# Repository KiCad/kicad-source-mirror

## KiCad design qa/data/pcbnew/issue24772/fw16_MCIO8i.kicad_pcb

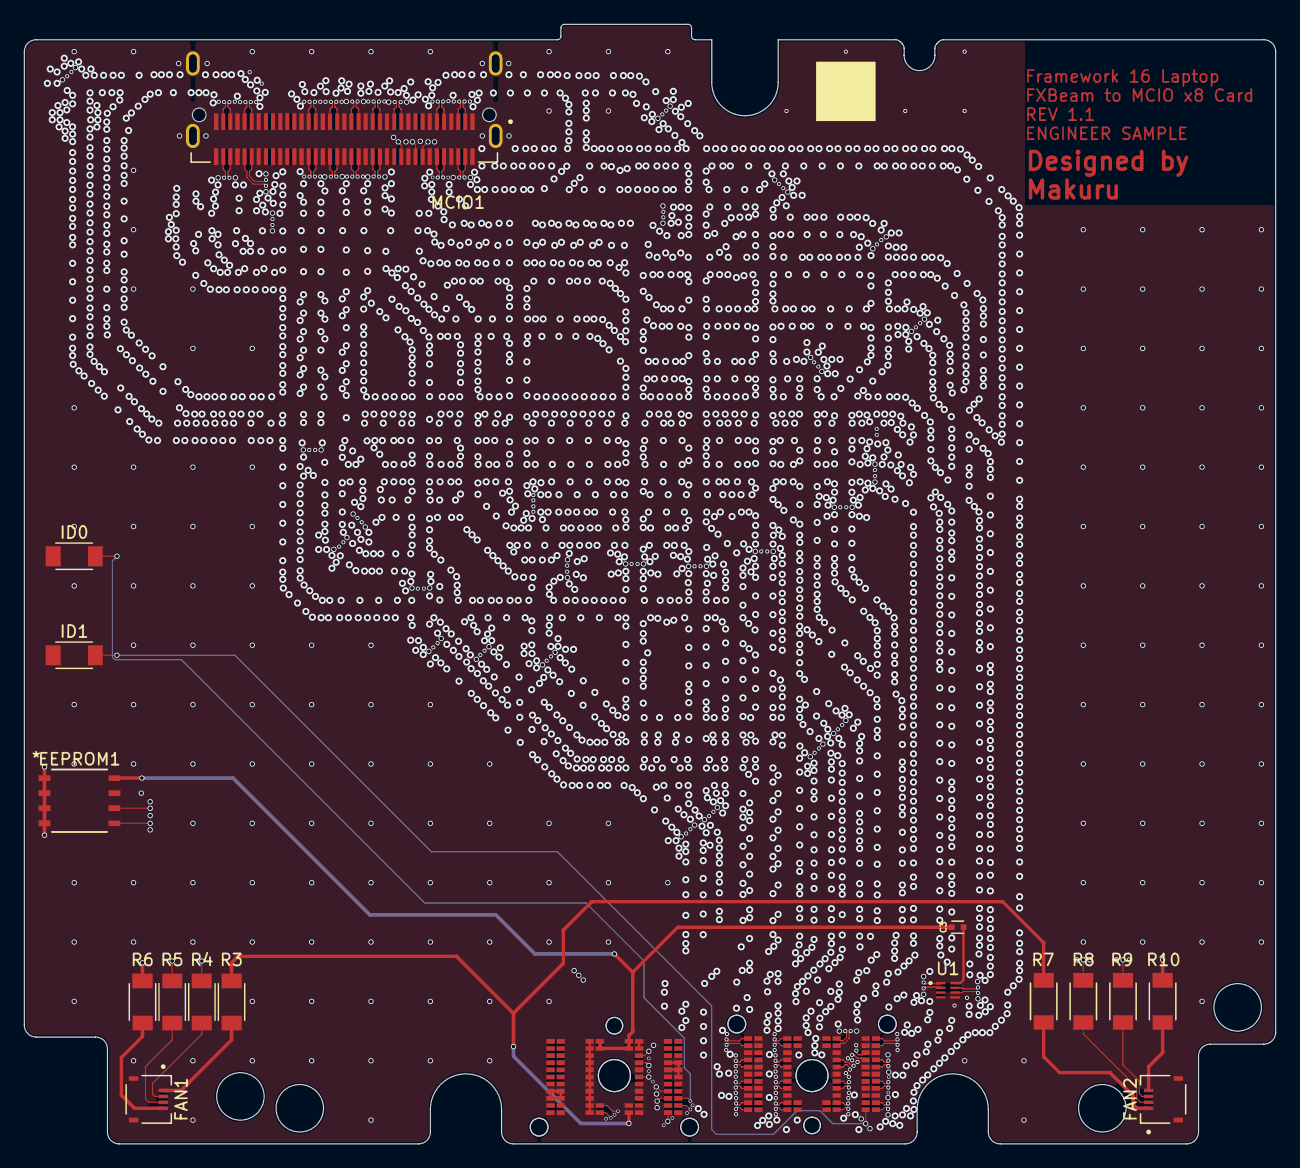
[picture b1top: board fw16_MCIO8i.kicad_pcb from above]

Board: 6 copper layers, 105.4 x 94.3 mm, 17 parts (0 on the bottom side), 60 nets.

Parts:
C3: 0402_885012105020; C_Wurth_WCAP-CSGP-0402
EEPROM1: BR24L32F-WE2; SOP8_ROM
FAN1, FAN2: F3311A7H121004E200; AMPHENOL_F3311A7H121004E200
ID0, ID1: 1206_R_560112132036; R_Wurth_WRIS-RSKS-1206_W
IN1: FXBEAM; FXBeam
MCIO1: G97R22312HR; AMPHENOL_G97R22312HR
R3, R4, R5, R6, R7, R8, R9, R10: 1206_R_560112132007; R_Wurth_WRIS-RSKS-1206_W
U1: SY75602ATWL-TR; VDFN8_NNC_MCH

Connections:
/MCIO/PCI.RX0+: IN1.SE8 (PEX_RX0P), MCIO1.A2 (PER0+)
/MCIO/PCI.RX0-: IN1.SD8 (PEX_RX0N), MCIO1.A3 (PER0-)
/MCIO/PCI.RX1+: IN1.SB8 (PEX_RX1P), MCIO1.A5 (PER1+)
/MCIO/PCI.RX1-: IN1.SA8 (PEX_RX1N), MCIO1.A6 (PER1-)
/MCIO/PCI.RX2+: IN1.SE6 (PEX_RX2P), MCIO1.A14 (PER2+)
/MCIO/PCI.RX2-: IN1.SD6 (PEX_RX2N), MCIO1.A15 (PER2-)
/MCIO/PCI.RX3+: IN1.SB6 (PEX_RX3P), MCIO1.A17 (PER3+)
/MCIO/PCI.RX3-: IN1.SA6 (PEX_RX3N), MCIO1.A18 (PER3-)
/MCIO/PCI.RX4+: IN1.SA3 (PEX_RX4P), MCIO1.A20 (PER4+)
/MCIO/PCI.RX4-: IN1.SB3 (PEX_RX4N), MCIO1.A21 (PER4-)
/MCIO/PCI.RX5+: IN1.SD3 (PEX_RX5P), MCIO1.A23 (PER5+)
/MCIO/PCI.RX5-: IN1.SE3 (PEX_RX5N), MCIO1.A24 (PER5-)
/MCIO/PCI.RX6+: IN1.SA1 (PEX_RX6P), MCIO1.A32 (PER6+)
/MCIO/PCI.RX6-: IN1.SB1 (PEX_RX6N), MCIO1.A33 (PER6-)
/MCIO/PCI.RX7+: IN1.SE1 (PEX_RX7P), MCIO1.A35 (PER7+)
/MCIO/PCI.RX7-: IN1.SD1 (PEX_RX7N), MCIO1.A36 (PER7-)
/MCIO/PCI.TX0+: IN1.SH8 (PEX_TX0P), MCIO1.B2 (PET0+)
/MCIO/PCI.TX0-: IN1.SG8 (PEX_TX0N), MCIO1.B3 (PET0-)
/MCIO/PCI.TX1+: IN1.SL8 (PEX_TX1P), MCIO1.B5 (PET1+)
/MCIO/PCI.TX1-: IN1.SK8 (PEX_TX1N), MCIO1.B6 (PET1-)
/MCIO/PCI.TX2+: IN1.SG6 (PEX_TX2P), MCIO1.B14 (PET2+)
/MCIO/PCI.TX2-: IN1.SH6 (PEX_TX2N), MCIO1.B15 (PET2-)
/MCIO/PCI.TX3+: IN1.SL6 (PEX_TX3P), MCIO1.B17 (PET3+)
/MCIO/PCI.TX3-: IN1.SK6 (PEX_TX3N), MCIO1.B18 (PET3-)
/MCIO/PCI.TX4+: IN1.SK3 (PEX_TX4P), MCIO1.B20 (PET4+)
/MCIO/PCI.TX4-: IN1.SL3 (PEX_TX4N), MCIO1.B21 (PET4-)
/MCIO/PCI.TX5+: IN1.SH3 (PEX_TX5P), MCIO1.B23 (PET5+)
/MCIO/PCI.TX5-: IN1.SG3 (PEX_TX5N), MCIO1.B24 (PET5-)
/MCIO/PCI.TX6+: IN1.SK1 (PEX_TX6P), MCIO1.B32 (PET6+)
/MCIO/PCI.TX6-: IN1.SL1 (PEX_TX6N), MCIO1.B33 (PET6-)
/MCIO/PCI.TX7+: IN1.SH1 (PEX_TX7P), MCIO1.B35 (PET7+)
/MCIO/PCI.TX7-: IN1.SG1 (PEX_TX7N), MCIO1.B36 (PET7-)
/MCIO/PEX.SCL: IN1.PL2 (DDS_CLK), MCIO1.B8 (SM_SCL)
/MCIO/PEX.SDA: IN1.PK1 (DDS_SDA), MCIO1.B9 (SM_SDA)
/MCIO/PEX_RETIME.CLK+: MCIO1.A11 (REFCLK+), U1.6 (OUT1_P)
/MCIO/PEX_RETIME.CLK-: MCIO1.A12 (REFCLK-), U1.7 (OUT1_N)
/PCIe-clk-mux/PEX.CLK+: IN1.SC2 (PEX_REFCLK+), U1.1 (IN_P)
/PCIe-clk-mux/PEX.CLK-: IN1.SD2 (PEX_REFCLK-), U1.2 (IN_N)
/PCIe-clk-mux/PWR.3V3: C3.1, EEPROM1.8 (Vcc), IN1.PA4 (3V3_ALW), IN1.PA5 (3V3_ALW), IN1.PB4 (3V3_ALW), IN1.PB5 (3V3_ALW)
/PCIe-clk-mux/PWR.5V: IN1.PK7 (5V_ALW), IN1.PK8 (5V_ALW), IN1.PL7 (5V_ALW), IN1.PL8 (5V_ALW)
/fxbeam/12V_PWR: IN1.PL4 (12V_FAN), R3.2, R7.2
/fxbeam/FAN0.PWM: IN1.PL5 (Fan0_PWM), R5.2
/fxbeam/FAN0.SPD: IN1.PH2 (Fan0_SPEED), R4.2
/fxbeam/FAN1.PWM: IN1.PK5 (Fan1_PWM), R9.2
/fxbeam/FAN1.SPD: IN1.PJ2 (Fan1_SPEED), R8.2
/fxbeam/I2C.SCL: EEPROM1.6 (SCL), IN1.PC3 (I2C_CLK_ALW)
/fxbeam/I2C.SDA: EEPROM1.5 (SDA), IN1.PD3 (I2C_DAT_ALW)
/fxbeam/PEX.RST: IN1.PF3 (PEX1_RST), MCIO1.B11 (PERST)
GND: EEPROM1.1 (A0), EEPROM1.2 (A1), EEPROM1.3 (A2), EEPROM1.4 (GND), EEPROM1.7 (WP), ID0.1, ID1.1, IN1.PA3 (GND), IN1.PA6 (GND), IN1.PB3 (GND), IN1.PB6 (GND), IN1.PC6 (GND), IN1.PD1 (GND), IN1.PD2 (GND), IN1.PD6 (GND), IN1.PE1 (GND), IN1.PE2 (GND), IN1.PE3 (GND), IN1.PE6 (GND), IN1.PF1 (GND), IN1.PF6 (GND), IN1.PG6 (GND), IN1.PH3 (GND), IN1.PH6 (GND), IN1.PH7 (GND), IN1.PH8 (GND), IN1.PJ6 (GND), IN1.PJ7 (GND), IN1.PJ8 (GND), IN1.PK4 (GND), IN1.PK6 (GND), IN1.PL3 (GND), IN1.PL6 (GND), IN1.SB2 (GND), IN1.SB7 (GND), IN1.SC1 (GND), IN1.SC3 (GND), IN1.SC6 (GND), IN1.SC8 (GND), IN1.SE2 (GND), IN1.SE7 (GND), IN1.SF1 (GND), IN1.SF3 (GND), IN1.SF6 (GND), IN1.SF8 (GND), IN1.SH2 (GND), IN1.SH7 (GND), IN1.SJ1 (GND), IN1.SJ3 (GND), IN1.SJ6 (GND), IN1.SJ8 (GND), MCIO1.A1 (GND), MCIO1.A4 (GND), MCIO1.A7 (GND), MCIO1.A10 (GND), MCIO1.A13 (GND), MCIO1.A16 (GND), MCIO1.A19 (GND), MCIO1.A22 (GND), MCIO1.A25 (GND), MCIO1.A28 (GND), MCIO1.A31 (GND), MCIO1.A34 (GND), MCIO1.A37 (GND), MCIO1.B1 (GND), MCIO1.B4 (GND), MCIO1.B7 (GND), MCIO1.B10 (GND), MCIO1.B13 (GND), MCIO1.B16 (GND), MCIO1.B19 (GND), MCIO1.B22 (GND), MCIO1.B25 (GND), MCIO1.B28 (GND), MCIO1.B31 (GND), MCIO1.B34 (GND), MCIO1.B37 (GND), MCIO1.SH1 (SHIELD), MCIO1.SH2 (SHIELD), MCIO1.SH3 (SHIELD), MCIO1.SH4 (SHIELD), R6.2, R10.2, U1.5 (GND)
unnamed: FAN1.1, R3.1
unnamed: FAN1.2, R4.1
unnamed: FAN1.3, R5.1
unnamed: FAN1.4, R6.1
unnamed: FAN2.1, R7.1
unnamed: FAN2.2, R8.1
unnamed: FAN2.3, R9.1
unnamed: FAN2.4, R10.1
unnamed: ID0.2, IN1.PJ1 (ID0)
unnamed: ID1.2, IN1.SL2 (ID1)
unnamed: C3.2, U1.8 (VDD)

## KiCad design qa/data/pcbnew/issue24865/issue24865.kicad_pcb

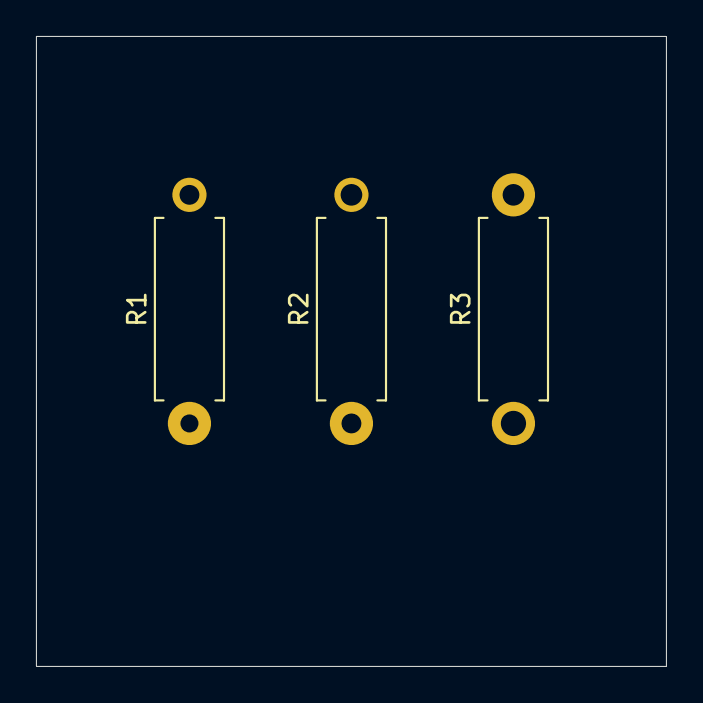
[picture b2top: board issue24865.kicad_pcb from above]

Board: 4 copper layers, 35.0 x 35.0 mm, 3 parts (0 on the bottom side), 2 nets, no tracks yet.

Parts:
R1: 5R; R_Axial_DIN0411_L9.9mm_D3.6mm_P12.70mm_Horizontal
R2: 10R; R_Axial_DIN0411_L9.9mm_D3.6mm_P12.70mm_Horizontal
R3: 15; R_Axial_DIN0411_L9.9mm_D3.6mm_P12.70mm_Horizontal

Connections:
+3V3: R1.1, R2.1, R3.1
GND: R1.2, R2.2, R3.2
